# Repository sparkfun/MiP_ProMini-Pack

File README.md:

SparkFun MiP ProMini-Pack
===========================

[*SparkFun MiP ProMini-Pack (DEV-13058)*](https://www.sparkfun.com/products/13058)

The MiP Robotic Platform is the first self-balancing robot that you can drive, dance, plays games, battle with other MiPs, and that you can control via a compatible iOS or Android device. 
With the SparkFun ProMini-Pack you can access the robot’s built-in hacking port to add increased functionality and a miniature Arduino to your MiP. 

Repository Contents
-------------------

* **/Hardware** - Eagle design files (.brd, .sch)
* **/Libraries** - Libraries for use with the <PRODUCT NAME>
* **/Production** - Production panel files (.brd)

Documentation
--------------
* **[Library](https://github.com/sparkfun/SparkFun_MiP_Arduino_Library)** - Arduino library for the MiP ProMini-Pack.
* **[Hookup Guide](https://learn.sparkfun.com/tutorials/hacking-the-mip---promini-pack)** - Basic hookup guide for the MiP ProMini-Pack.
* **[SparkFun Fritzing repo](https://github.com/sparkfun/Fritzing_Parts)** - Fritzing diagrams for SparkFun products.
* **[SparkFun 3D Model repo](https://github.com/sparkfun/3D_Models)** - 3D models of SparkFun products. 
* **[SparkFun Graphical Datasheets](https://github.com/sparkfun/Graphical_Datasheets)** -Graphical Datasheets for various SparkFun products.

License Information
-------------------

This product is _**open source**_! 

Please review the LICENSE.md file for license information. 

If you have any questions or concerns on licensing, please contact techsupport@sparkfun.com.

Distributed as-is; no warranty is given.

- Your friends at SparkFun.

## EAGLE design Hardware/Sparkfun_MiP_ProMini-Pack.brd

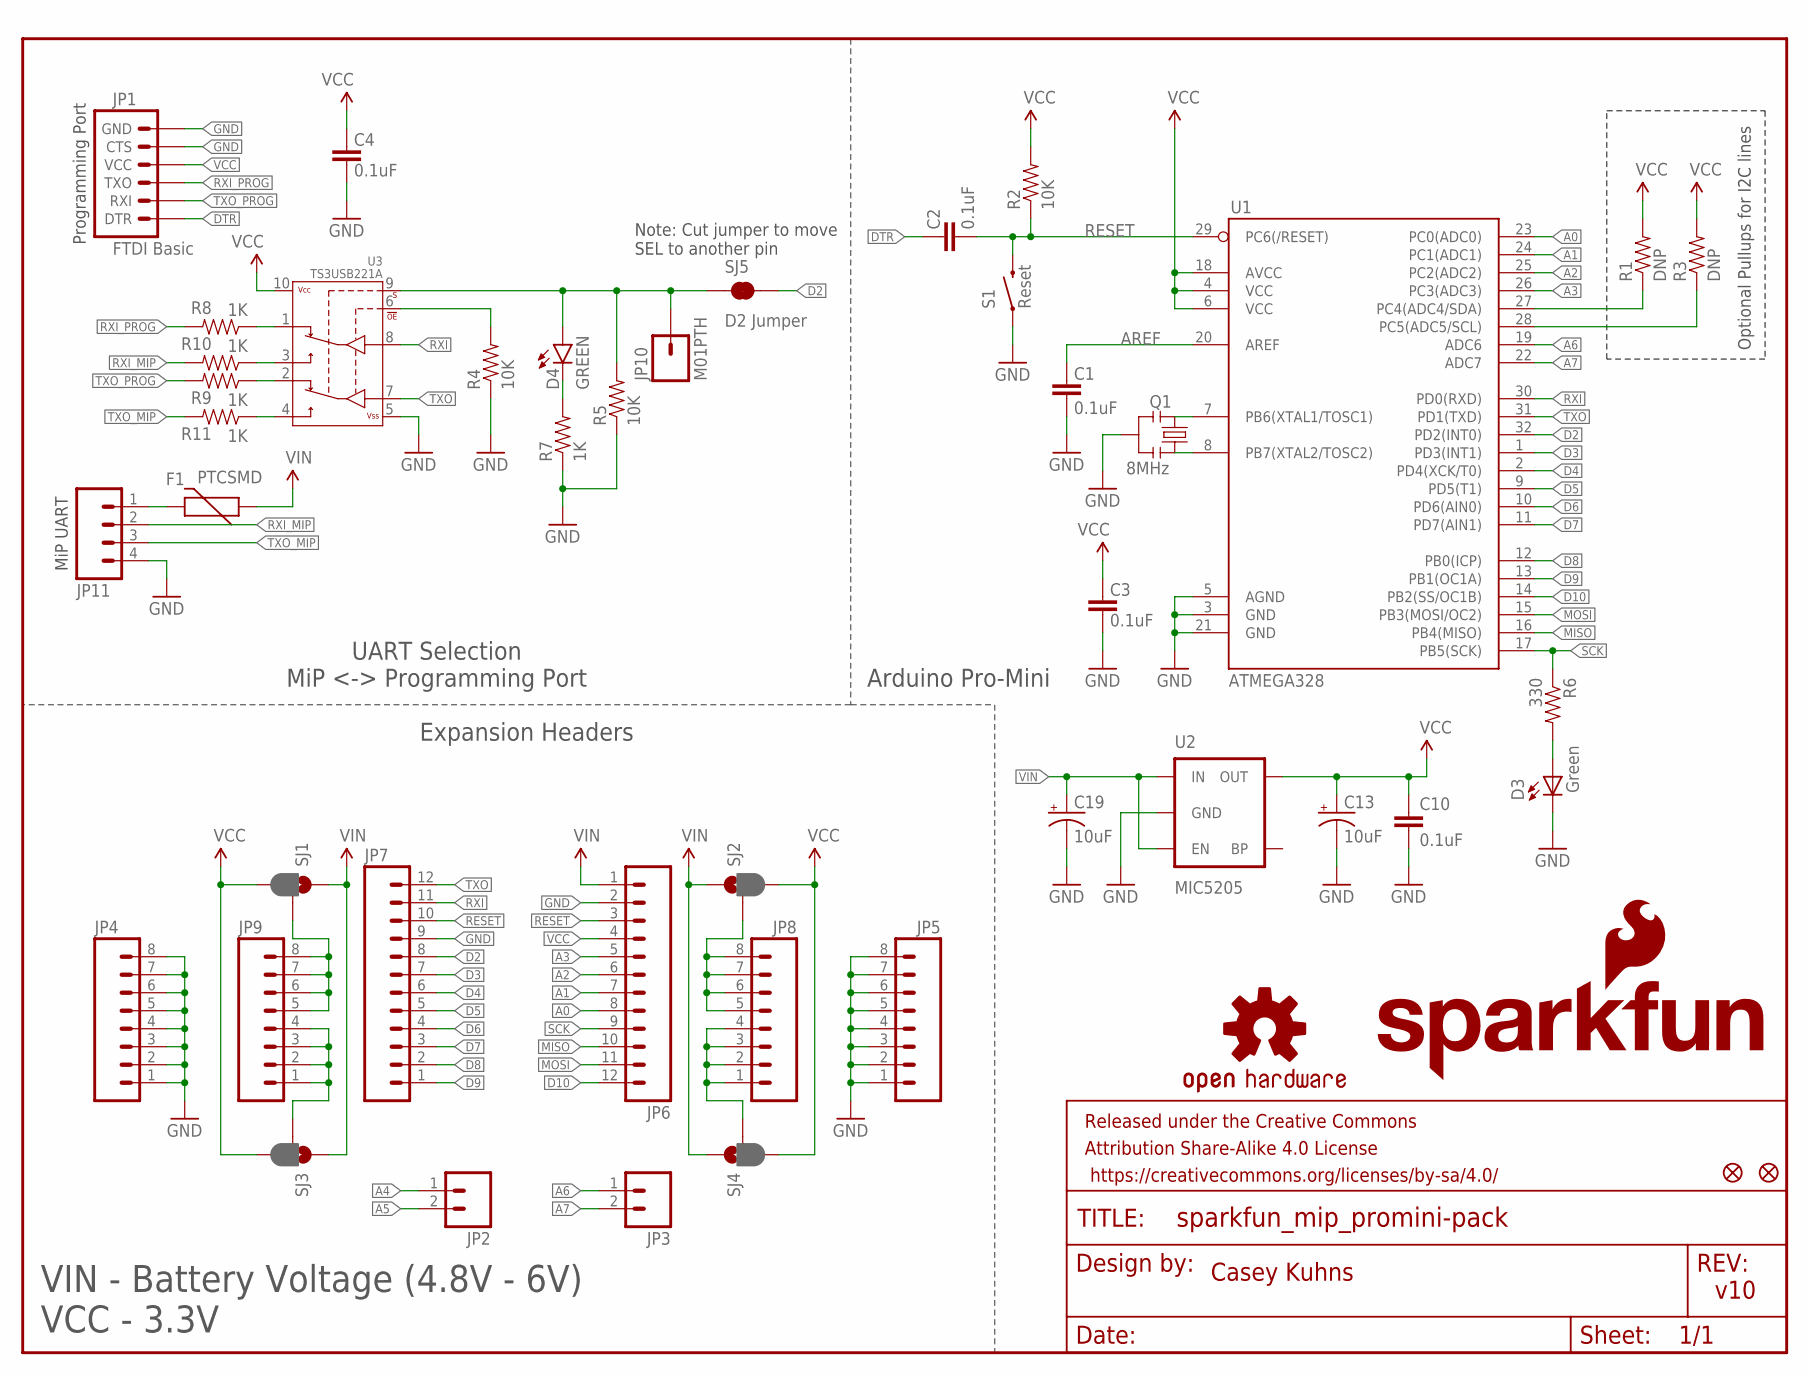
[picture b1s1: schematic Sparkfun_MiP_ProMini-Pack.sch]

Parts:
C1, C2, C3, C4, C10: 0.1uF; 0603-CAP
C13, C19: 10uF; EIA3216
D3: Green; 0603-LED-ALT1
D4: GREEN; LED-0603
F1: PTCSMD; PTC-1206
FID1, FID2: FIDUCIAL1X2; FIDUCIAL-1X2
FRAME1: FRAME-LETTER; CREATIVE_COMMONS
JP1: FTDI Basic; 1X06
JP2, JP3: M02PTH; 1X02
JP4, JP5, JP8, JP9: M081X08; 1X08
JP6, JP7: M12PTH; 1X12
JP10: M01PTH; 1X01
JP11: M04JST; 1X04-1.5MM_JST
LOGO1: SFE_LOGO_NAME_FLAME.1_INCH; SFE_LOGO_NAME_FLAME_.1
LOGO2: OSHW-LOGOS; OSHW-LOGO-S
Q1: 8MHz; RESONATOR-SMD
R1, R3: DNP; 0603-RES
R2, R4, R5: 10K; 0603-RES
R6: 330; 0603-RES
R7, R8, R9, R10, R11: 1K; 0603-RES
S1: Reset; TACTILE-SWITCH-SMD-ALT01
SJ1, SJ2, SJ3, SJ4: JUMPER-PAD-3-2OF3_NC_BY_PASTE; PAD-JUMPER-3-2OF3_NC_BY_PASTE_YES_SILK_FULL_BOX
SJ5: D2 Jumper; PAD-JUMPER-2-NC_BY_TRACE_YES_SILK
U1: ATMEGA328; TQFP32-08
U2: MIC5205; SOT23-5
U3: TS3USB221A; QFN-10-RSE

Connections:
A0: JP6.8, U1.23 (PC0(ADC0))
A1: JP6.7, U1.24 (PC1(ADC1))
A2: JP6.6, U1.25 (PC2(ADC2))
A3: JP6.5, U1.26 (PC3(ADC3))
A4: JP2.1, R1.1, U1.27 (PC4(ADC4/SDA))
A5: JP2.2, R3.1, U1.28 (PC5(ADC5/SCL))
A6: JP3.1, U1.19 (ADC6)
A7: JP3.2, U1.22 (ADC7)
AREF: C1.2, U1.20 (AREF)
D2: JP7.8, SJ5.2, U1.32 (PD2(INT0))
D3: JP7.7, U1.1 (PD3(INT1))
D4: JP7.6, U1.2 (PD4(XCK/T0))
D5: JP7.5, U1.9 (PD5(T1))
D6: JP7.4, U1.10 (PD6(AIN0))
D7: JP7.3, U1.11 (PD7(AIN1))
D8: JP7.2, U1.12 (PB0(ICP))
D9: JP7.1, U1.13 (PB1(OC1A))
D10: JP6.12, U1.14 (PB2(SS/OC1B))
DTR: C2.2, JP1.1 (DTR)
GND: C1.1, C3.1, C4.1, C10.2, C13.C (-), C19.C (-), D3.C, JP1.5 (CTS), JP1.6 (GND), JP4.1, JP4.2, JP4.3, JP4.4, JP4.5, JP4.6, JP4.7, JP4.8, JP5.1, JP5.2, JP5.3, JP5.4, JP5.5, JP5.6, JP5.7, JP5.8, JP6.2, JP7.9, JP11.4, Q1.2, R4.1, R5.1, R7.1, S1.1, U1.3 (GND), U1.5 (AGND), U1.21 (GND), U2.2 (GND), U3.5 (VSS)
MISO: JP6.10, U1.16 (PB4(MISO))
MOSI: JP6.11, U1.15 (PB3(MOSI/OC2))
unnamed: Q1.3, U1.8 (PB7(XTAL2/TOSC2))
unnamed: JP9.5, JP9.6, JP9.7, JP9.8, SJ1.2
unnamed: JP9.1, JP9.2, JP9.3, JP9.4, SJ3.2
unnamed: Q1.1, U1.7 (PB6(XTAL1/TOSC1))
unnamed: JP8.5, JP8.6, JP8.7, JP8.8, SJ2.2
unnamed: JP8.1, JP8.2, JP8.3, JP8.4, SJ4.2
unnamed: D3.A, R6.2
unnamed: D4.C, R7.2
unnamed: R10.1, U3.3 (2D+)
unnamed: R11.1, U3.4 (2D-)
unnamed: R8.1, U3.1 (1D+)
unnamed: R4.2, U3.6 (!OE)
unnamed: R9.1, U3.2 (1D-)
unnamed: F1.2, JP11.1
RESET: C2.1, JP6.3, JP7.10, R2.1, S1.3 (2), U1.29 (PC6(/RESET))
RXI: JP7.11, U1.30 (PD0(RXD)), U3.8 (D+)
RXI_MIP: JP11.2, R10.2
RXI_PROG: JP1.3 (TXO), R8.2
SCK: JP6.9, R6.1, U1.17 (PB5(SCK))
SELECT: D4.A, JP10.1, R5.2, SJ5.1, U3.9 (S)
TXO: JP7.12, U1.31 (PD1(TXD)), U3.7 (D-)
TXO_MIP: JP11.3, R11.2
TXO_PROG: JP1.2 (RXI), R9.2
VCC: C3.2, C4.2, C10.1, C13.A (+), JP1.4 (VCC), JP6.4, R1.2, R2.2, R3.2, SJ1.3, SJ2.3, SJ3.3, SJ4.3, U1.4 (VCC), U1.6 (VCC), U1.18 (AVCC), U2.5 (OUT), U3.10 (VCC)
VIN: C19.A (+), F1.1, JP6.1, SJ1.1, SJ2.1, SJ3.1, SJ4.1, U2.1 (IN), U2.3 (EN)

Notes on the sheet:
Optional Pullups for I2C lines
Casey Kuhns
v10
Note: Cut jumper to move SEL to another pin
MiP UART
Programming Port
UART Selection MiP <-> Programming Port
Expansion Headers
Arduino Pro-Mini
VIN - Battery Voltage (4.8V - 6V) VCC - 3.3V

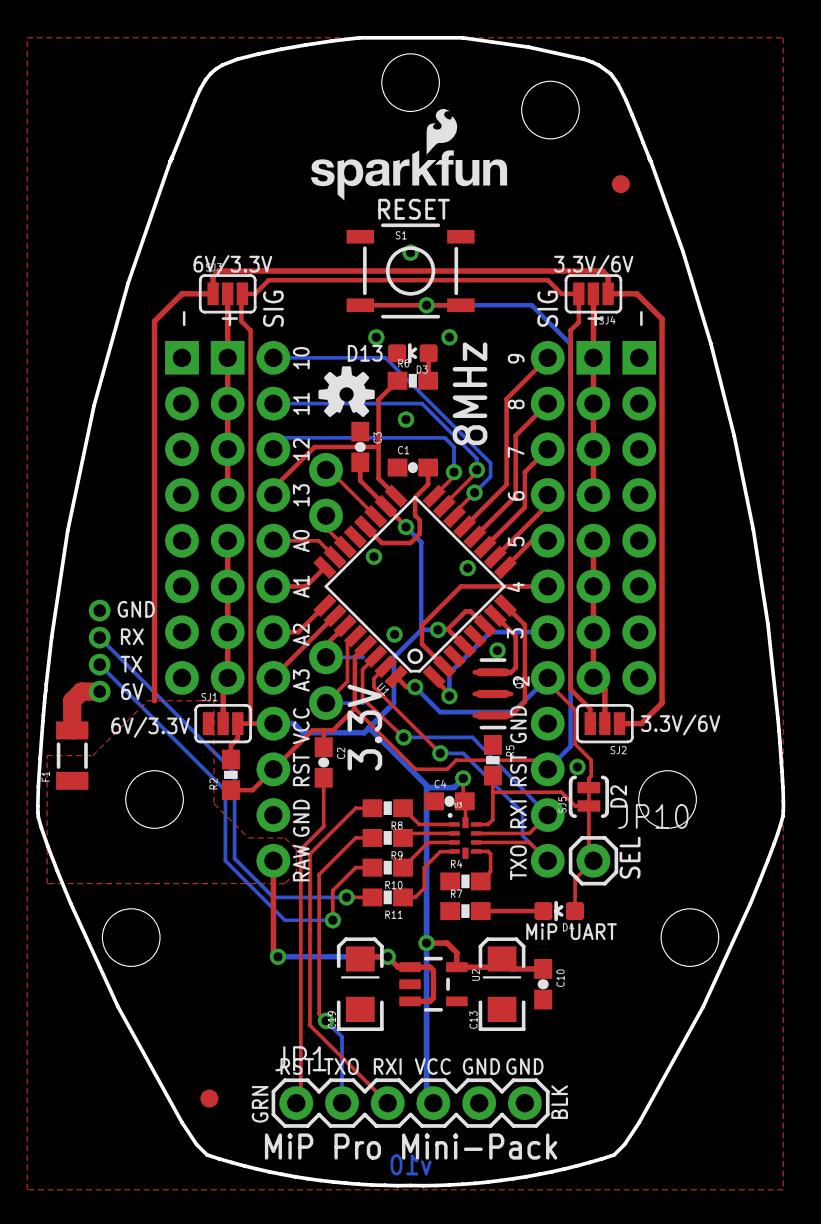
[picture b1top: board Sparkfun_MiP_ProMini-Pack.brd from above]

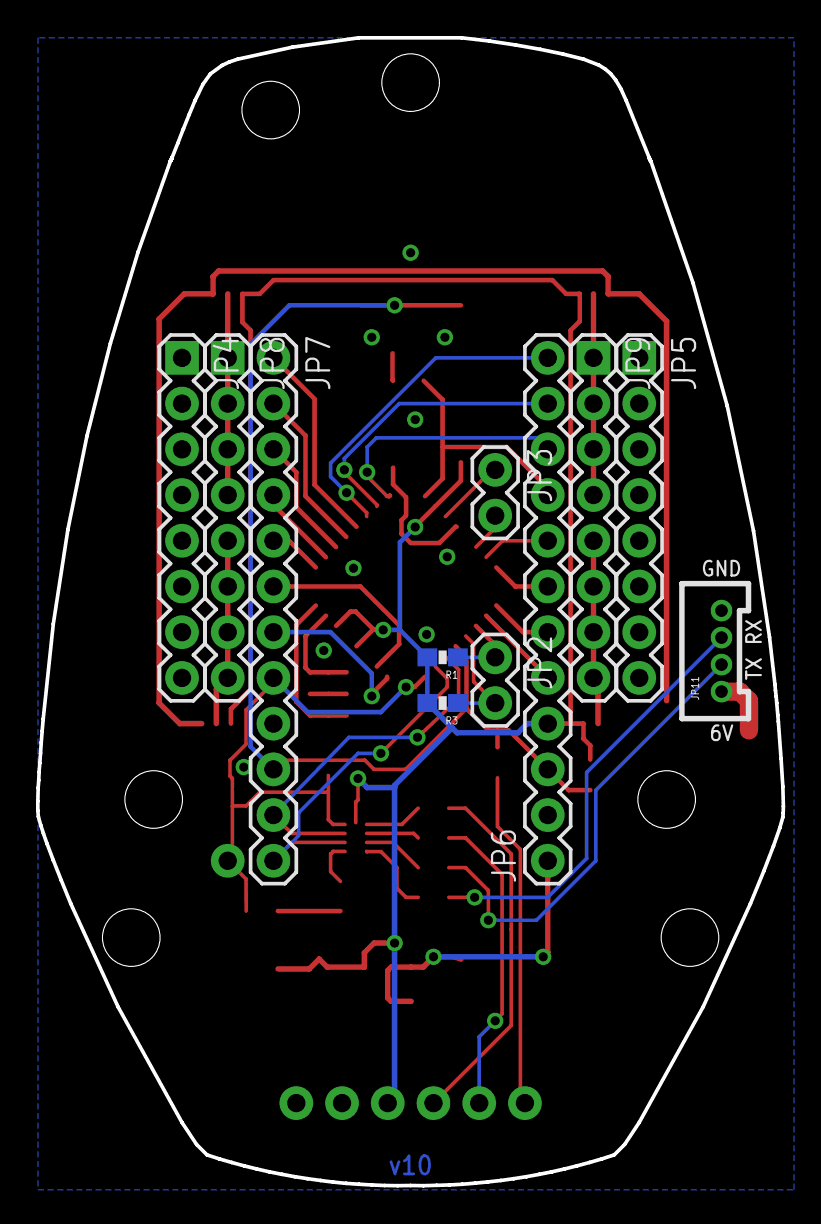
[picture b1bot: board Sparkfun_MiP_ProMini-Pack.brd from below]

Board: 2 copper layers, 41.4 x 63.8 mm, 47 parts (11 on the bottom side), 47 nets.

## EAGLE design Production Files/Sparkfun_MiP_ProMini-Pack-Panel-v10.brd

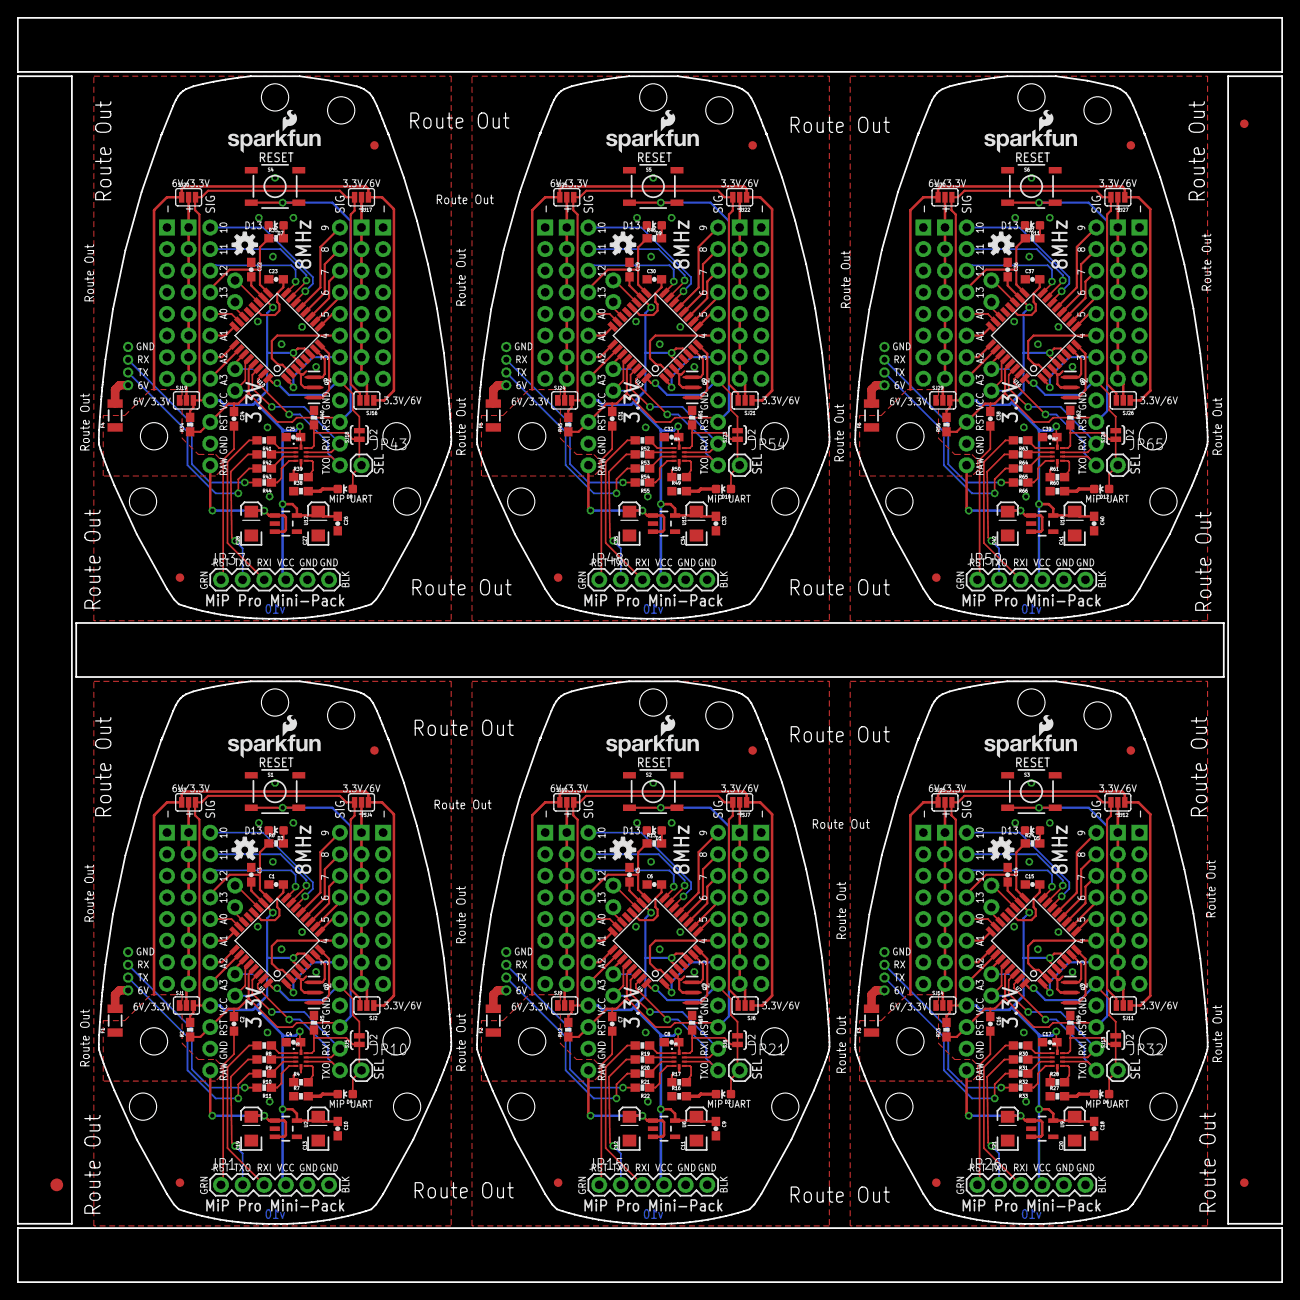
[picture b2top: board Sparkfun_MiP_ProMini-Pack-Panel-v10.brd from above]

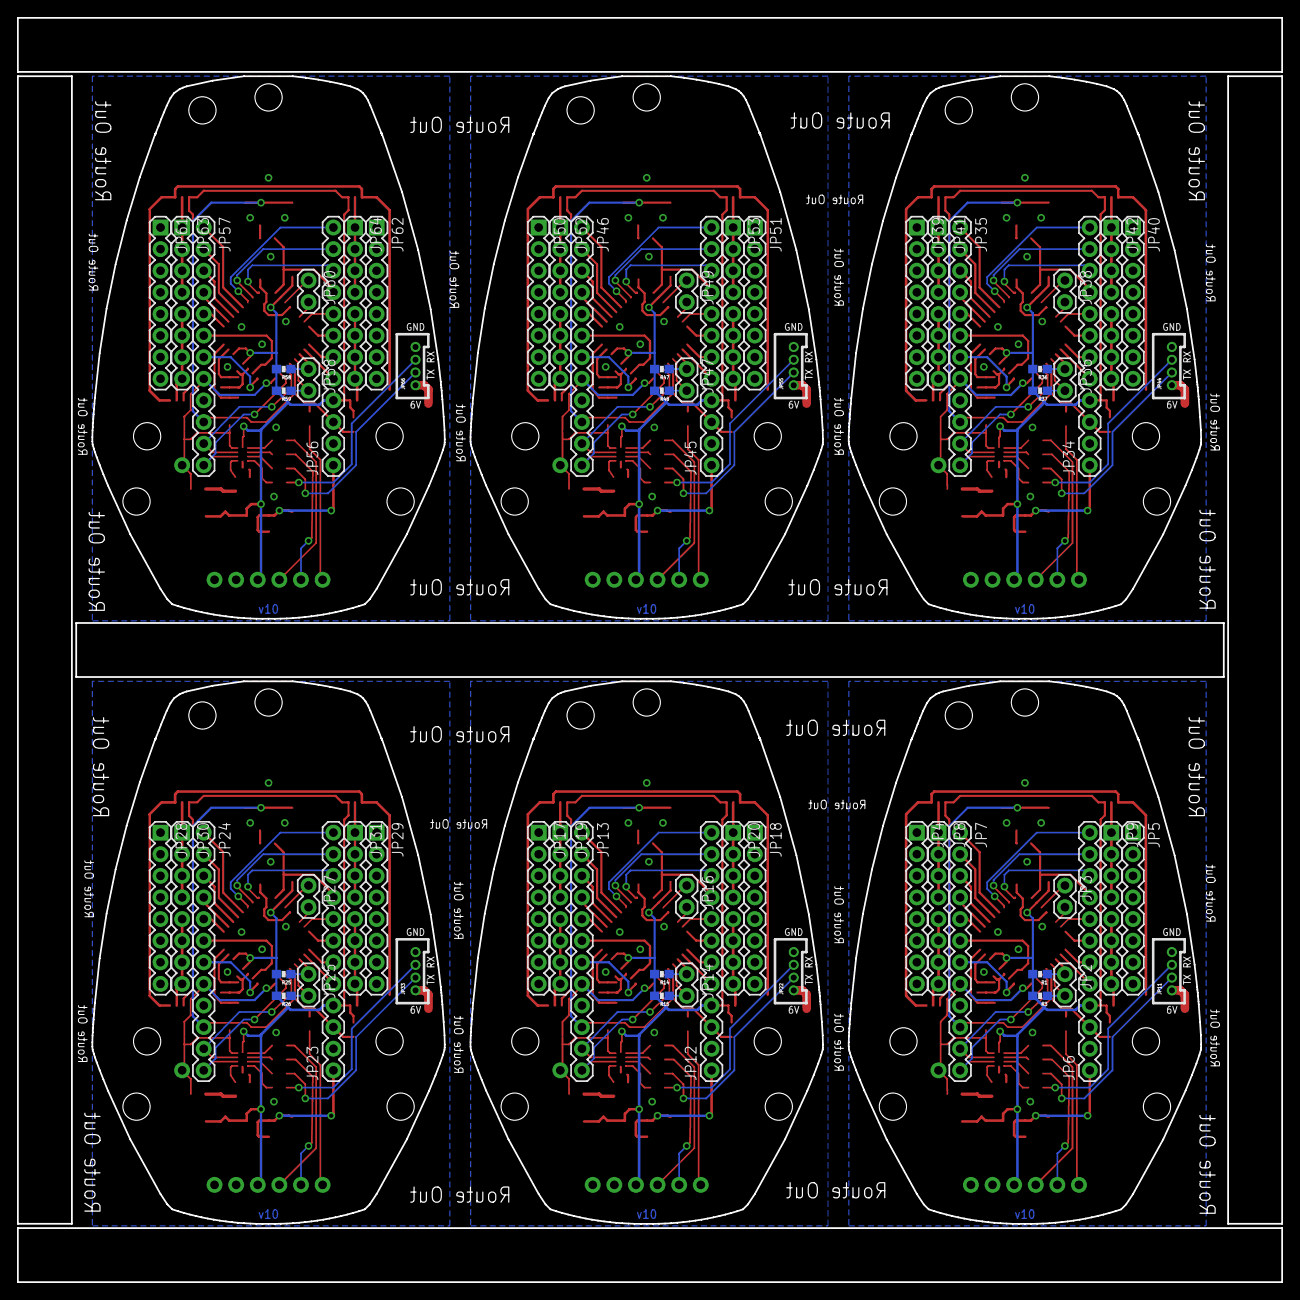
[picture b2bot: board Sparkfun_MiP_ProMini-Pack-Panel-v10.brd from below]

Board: 2 copper layers, 148.6 x 148.6 mm, 279 parts (66 on the bottom side), 282 nets.

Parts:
C1, C2, C3, C4, C5, C6, C7, C8, C9, C10, C14, C15, C16, C17, C18, C22, C23, C24, C25, C26, C29, C30, C31, C32, C33, C36, C37, C38, C39, C40: 0.1uF; 0603-CAP
C11, C12, C13, C19, C20, C21, C27, C28, C34, C35, C41, C42: 10uF; EIA3216
D1, D3, D5, D7, D9, D11: Green; LED-0603
D2, D4, D6, D8, D10, D12: GREEN; LED-0603
E$1: FIDUCIAL-1.5X3
E$4, E$10: FIDUCIAL-1X2
F1, F2, F3, F4, F5, F6: PTCSMD; PTC-1206
FID1, FID2, FID3, FID4, FID5, FID6, FID7, FID8, FID9, FID10, FID11, FID12: FIDUCIAL1X2; FIDUCIAL-1X2
JP1, JP15, JP26, JP37, JP48, JP59: FTDI Basic; 1X06
JP2, JP3, JP14, JP16, JP25, JP27, JP36, JP38, JP47, JP49, JP58, JP60: 1X02
JP4, JP5, JP8, JP9, JP17, JP18, JP19, JP20, JP28, JP29, JP30, JP31, JP39, JP40, JP41, JP42, JP50, JP51, JP52, JP53, JP61, JP62, JP63, JP64: 1X08
JP6, JP7, JP12, JP13, JP23, JP24, JP34, JP35, JP45, JP46, JP56, JP57: 1X12
JP10, JP21, JP32, JP43, JP54, JP65: M01PTH; 1X01
JP11, JP22, JP33, JP44, JP55, JP66: 1X04-1.5MM_JST
LOGO1, LOGO3, LOGO5, LOGO7, LOGO9, LOGO11: SFE_LOGO_NAME_FLAME.1_INCH; SFE_LOGO_NAME_FLAME_.1
LOGO2, LOGO4, LOGO6, LOGO8, LOGO10, LOGO12: OSHW-LOGOS; OSHW-LOGO-S
Q1, Q2, Q3, Q4, Q5, Q6: 8MHz; RESONATOR-SMD
R1, R3, R14, R15, R25, R26, R36, R37, R47, R48, R58, R59: DNP; 0603-RES
R2, R4, R5, R12, R17, R18, R23, R28, R29, R34, R39, R40, R45, R50, R51, R56, R61, R62: 10K; 0603-RES
R6, R13, R24, R35, R46, R57: 330; 0603-RES
R7, R8, R9, R10, R11, R16, R19, R20, R21, R22, R27, R30, R31, R32, R33, R38, R41, R42, R43, R44, R49, R52, R53, R54, R55, R60, R63, R64, R65, R66: 1K; 0603-RES
S1, S2, S3, S4, S5, S6: Reset; TACTILE-SWITCH-SMD
SJ1, SJ2, SJ3, SJ4, SJ6, SJ7, SJ9, SJ10, SJ11, SJ12, SJ14, SJ15, SJ16, SJ17, SJ19, SJ20, SJ21, SJ22, SJ24, SJ25, SJ26, SJ27, SJ29, SJ30: PAD-JUMPER-3-2OF3_NC_BY_PASTE_YES_SILK_FULL_BOX
SJ5, SJ8, SJ13, SJ18, SJ23, SJ28: D2 Jumper; PAD-JUMPER-2-NC_BY_TRACE_YES_SILK
U1, U4, U7, U10, U13, U16: ATMEGA328; TQFP32-08
U2, U6, U9, U12, U15, U18: MIC5205; SOT23-5
U3, U5, U8, U11, U14, U17: TS3USB221A; QFN-10-RSE

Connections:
A0: JP6.8, U1.23
A1: JP6.7, U1.24
A2: JP6.6, U1.25
A3: JP6.5, U1.26
A4: JP2.1, R1.1, U1.27
A5: JP2.2, R3.1, U1.28
A6: JP3.1, U1.19
A7: JP3.2, U1.22
A8: JP14.2, R15.1, U4.28
A9: JP14.1, R14.1, U4.27
A10: JP12.5, U4.26
A11: JP12.6, U4.25
A12: JP12.7, U4.24
A13: JP12.8, U4.23
A14: JP16.1, U4.19
A15: JP16.2, U4.22
A16: JP25.2, R26.1, U7.28
A17: JP25.1, R25.1, U7.27
A18: JP23.5, U7.26
A19: JP23.6, U7.25
A20: JP23.7, U7.24
A21: JP23.8, U7.23
A22: JP27.1, U7.19
A23: JP27.2, U7.22
A24: JP36.2, R37.1, U10.28
A25: JP36.1, R36.1, U10.27
A26: JP34.5, U10.26
A27: JP34.6, U10.25
A28: JP34.7, U10.24
A29: JP34.8, U10.23
A30: JP38.1, U10.19
A31: JP38.2, U10.22
A32: JP47.2, R48.1, U13.28
A33: JP47.1, R47.1, U13.27
A34: JP45.5, U13.26
A35: JP45.6, U13.25
A36: JP45.7, U13.24
A37: JP45.8, U13.23
A38: JP49.1, U13.19
A39: JP49.2, U13.22
A40: JP58.2, R59.1, U16.28
A41: JP58.1, R58.1, U16.27
A42: JP56.5, U16.26
A43: JP56.6, U16.25
A44: JP56.7, U16.24
A45: JP56.8, U16.23
A46: JP60.1, U16.19
A47: JP60.2, U16.22
AREF: C1.2, U1.20
AREF1: C6.2, U4.20
AREF2: C15.2, U7.20
AREF3: C23.2, U10.20
AREF4: C30.2, U13.20
AREF5: C37.2, U16.20
D1: JP13.1, U4.13
D2: JP7.8, SJ5.2, U1.32
D3: JP7.7, U1.1
D4: JP7.6, U1.2
D5: JP7.5, U1.9
D6: JP7.4, U1.10
D7: JP7.3, U1.11
D8: JP7.2, U1.12
D9: JP7.1, U1.13
D10: JP6.12, U1.14
D11: JP13.2, U4.12
D12: JP13.8, SJ8.2, U4.32
D13: JP13.7, U4.1
D14: JP13.6, U4.2
D15: JP13.5, U4.9
D16: JP13.4, U4.10
D17: JP13.3, U4.11
D18: JP12.12, U4.14
D19: JP24.1, U7.13
D20: JP24.2, U7.12
D21: JP24.8, SJ13.2, U7.32
D22: JP24.7, U7.1
D23: JP24.6, U7.2
D24: JP24.5, U7.9
D25: JP24.4, U7.10
D26: JP24.3, U7.11
D27: JP23.12, U7.14
D28: JP35.1, U10.13
D29: JP35.2, U10.12
D30: JP35.8, SJ18.2, U10.32
D31: JP35.7, U10.1
D32: JP35.6, U10.2
D33: JP35.5, U10.9
D34: JP35.4, U10.10
D35: JP35.3, U10.11
D36: JP34.12, U10.14
D37: JP46.1, U13.13
D38: JP46.2, U13.12
D39: JP46.8, SJ23.2, U13.32
D40: JP46.7, U13.1
D41: JP46.6, U13.2
D42: JP46.5, U13.9
D43: JP46.4, U13.10
D44: JP46.3, U13.11
D45: JP45.12, U13.14
D46: JP57.1, U16.13
D47: JP57.2, U16.12
D48: JP57.8, SJ28.2, U16.32
D49: JP57.7, U16.1
D50: JP57.6, U16.2
D51: JP57.5, U16.9
D52: JP57.4, U16.10
D53: JP57.3, U16.11
D54: JP56.12, U16.14
DTR: C2.2, JP1.1
DTR1: C7.2, JP15.1
DTR2: C16.2, JP26.1
DTR3: C24.2, JP37.1
DTR4: C31.2, JP48.1
DTR5: C38.2, JP59.1
GND: C1.1, C3.1, C4.1, C10.2, C13.C, C19.C, D3.C, JP1.5, JP1.6, JP4.1, JP4.2, JP4.3, JP4.4, JP4.5, JP4.6, JP4.7, JP4.8, JP5.1, JP5.2, JP5.3, JP5.4, JP5.5, JP5.6, JP5.7, JP5.8, JP6.2, JP7.9, JP11.4, Q1.2, R4.1, R5.1, R7.1, S1.1, U1.3, U1.5, U1.21, U2.2, U3.5
GND1: C5.1, C6.1, C8.1, C9.2, C11.C, C12.C, D1.C, JP12.2, JP13.9, JP15.5, JP15.6, JP17.1, JP17.2, JP17.3, JP17.4, JP17.5, JP17.6, JP17.7, JP17.8, JP18.1, JP18.2, JP18.3, JP18.4, JP18.5, JP18.6, JP18.7, JP18.8, JP22.4, Q2.2, R16.1, R17.1, R18.1, S2.1, U4.3, U4.5, U4.21, U5.5, U6.2
GND2: C14.1, C15.1, C17.1, C18.2, C20.C, C21.C, D5.C, JP23.2, JP24.9, JP26.5, JP26.6, JP28.1, JP28.2, JP28.3, JP28.4, JP28.5, JP28.6, JP28.7, JP28.8, JP29.1, JP29.2, JP29.3, JP29.4, JP29.5, JP29.6, JP29.7, JP29.8, JP33.4, Q3.2, R27.1, R28.1, R29.1, S3.1, U7.3, U7.5, U7.21, U8.5, U9.2
GND3: C22.1, C23.1, C25.1, C26.2, C27.C, C28.C, D7.C, JP34.2, JP35.9, JP37.5, JP37.6, JP39.1, JP39.2, JP39.3, JP39.4, JP39.5, JP39.6, JP39.7, JP39.8, JP40.1, JP40.2, JP40.3, JP40.4, JP40.5, JP40.6, JP40.7, JP40.8, JP44.4, Q4.2, R38.1, R39.1, R40.1, S4.1, U10.3, U10.5, U10.21, U11.5, U12.2
GND4: C29.1, C30.1, C32.1, C33.2, C34.C, C35.C, D9.C, JP45.2, JP46.9, JP48.5, JP48.6, JP50.1, JP50.2, JP50.3, JP50.4, JP50.5, JP50.6, JP50.7, JP50.8, JP51.1, JP51.2, JP51.3, JP51.4, JP51.5, JP51.6, JP51.7, JP51.8, JP55.4, Q5.2, R49.1, R50.1, R51.1, S5.1, U13.3, U13.5, U13.21, U14.5, U15.2
GND5: C36.1, C37.1, C39.1, C40.2, C41.C, C42.C, D11.C, JP56.2, JP57.9, JP59.5, JP59.6, JP61.1, JP61.2, JP61.3, JP61.4, JP61.5, JP61.6, JP61.7, JP61.8, JP62.1, JP62.2, JP62.3, JP62.4, JP62.5, JP62.6, JP62.7, JP62.8, JP66.4, Q6.2, R60.1, R61.1, R62.1, S6.1, U16.3, U16.5, U16.21, U17.5, U18.2
MISO: JP6.10, U1.16
MISO1: JP12.10, U4.16
MISO2: JP23.10, U7.16
MISO3: JP34.10, U10.16
MISO4: JP45.10, U13.16
MISO5: JP56.10, U16.16
MOSI: JP6.11, U1.15
MOSI1: JP12.11, U4.15
MOSI2: JP23.11, U7.15
MOSI3: JP34.11, U10.15
MOSI4: JP45.11, U13.15
MOSI5: JP56.11, U16.15
unnamed: Q1.3, U1.8
unnamed: JP9.5, JP9.6, JP9.7, JP9.8, SJ1.2
unnamed: JP9.1, JP9.2, JP9.3, JP9.4, SJ3.2
unnamed: Q1.1, U1.7
unnamed: JP8.5, JP8.6, JP8.7, JP8.8, SJ2.2
unnamed: JP8.1, JP8.2, JP8.3, JP8.4, SJ4.2
unnamed: D3.A, R6.2
unnamed: D4.C, R7.2
unnamed: R10.1, U3.3
unnamed: R11.1, U3.4
unnamed: R8.1, U3.1
unnamed: R4.2, U3.6
unnamed: R9.1, U3.2
unnamed: D1.A, R13.2
unnamed: Q2.3, U4.8
unnamed: F1.2, JP11.1
unnamed: Q2.1, U4.7
unnamed: JP19.5, JP19.6, JP19.7, JP19.8, SJ6.2
unnamed: JP20.5, JP20.6, JP20.7, JP20.8, SJ9.2
unnamed: JP20.1, JP20.2, JP20.3, JP20.4, SJ10.2
unnamed: JP19.1, JP19.2, JP19.3, JP19.4, SJ7.2
unnamed: D2.C, R16.2
unnamed: R17.2, U5.6
unnamed: R19.1, U5.1
unnamed: R20.1, U5.2
unnamed: R21.1, U5.3
unnamed: R22.1, U5.4
unnamed: F2.2, JP22.1
unnamed: D5.A, R24.2
unnamed: Q3.3, U7.8
unnamed: Q3.1, U7.7
unnamed: JP30.5, JP30.6, JP30.7, JP30.8, SJ11.2
unnamed: JP31.5, JP31.6, JP31.7, JP31.8, SJ14.2
unnamed: JP31.1, JP31.2, JP31.3, JP31.4, SJ15.2
unnamed: JP30.1, JP30.2, JP30.3, JP30.4, SJ12.2
unnamed: D6.C, R27.2
unnamed: R28.2, U8.6
unnamed: R30.1, U8.1
unnamed: R31.1, U8.2
unnamed: R32.1, U8.3
unnamed: R33.1, U8.4
unnamed: F3.2, JP33.1
unnamed: D7.A, R35.2
unnamed: Q4.3, U10.8
unnamed: Q4.1, U10.7
unnamed: JP41.5, JP41.6, JP41.7, JP41.8, SJ16.2
unnamed: JP42.5, JP42.6, JP42.7, JP42.8, SJ19.2
unnamed: JP42.1, JP42.2, JP42.3, JP42.4, SJ20.2
unnamed: JP41.1, JP41.2, JP41.3, JP41.4, SJ17.2
unnamed: D8.C, R38.2
unnamed: R39.2, U11.6
unnamed: R41.1, U11.1
unnamed: R42.1, U11.2
unnamed: R43.1, U11.3
unnamed: R44.1, U11.4
unnamed: F4.2, JP44.1
unnamed: D9.A, R46.2
unnamed: Q5.3, U13.8
unnamed: Q5.1, U13.7
unnamed: JP52.5, JP52.6, JP52.7, JP52.8, SJ21.2
unnamed: JP53.5, JP53.6, JP53.7, JP53.8, SJ24.2
unnamed: JP53.1, JP53.2, JP53.3, JP53.4, SJ25.2
unnamed: JP52.1, JP52.2, JP52.3, JP52.4, SJ22.2
unnamed: D10.C, R49.2
unnamed: R50.2, U14.6
unnamed: R52.1, U14.1
unnamed: R53.1, U14.2
unnamed: R54.1, U14.3
unnamed: R55.1, U14.4
unnamed: F5.2, JP55.1
unnamed: D11.A, R57.2
unnamed: Q6.3, U16.8
unnamed: Q6.1, U16.7
unnamed: JP63.5, JP63.6, JP63.7, JP63.8, SJ26.2
unnamed: JP64.5, JP64.6, JP64.7, JP64.8, SJ29.2
unnamed: JP64.1, JP64.2, JP64.3, JP64.4, SJ30.2
unnamed: JP63.1, JP63.2, JP63.3, JP63.4, SJ27.2
unnamed: D12.C, R60.2
unnamed: R61.2, U17.6
unnamed: R63.1, U17.1
unnamed: R64.1, U17.2
unnamed: R65.1, U17.3
unnamed: R66.1, U17.4
unnamed: F6.2, JP66.1
RESET: C2.1, JP6.3, JP7.10, R2.1, S1.3, U1.29
RESET1: C7.1, JP12.3, JP13.10, R12.1, S2.3, U4.29
RESET2: C16.1, JP23.3, JP24.10, R23.1, S3.3, U7.29
RESET3: C24.1, JP34.3, JP35.10, R34.1, S4.3, U10.29
RESET4: C31.1, JP45.3, JP46.10, R45.1, S5.3, U13.29
RESET5: C38.1, JP56.3, JP57.10, R56.1, S6.3, U16.29
RXI: JP7.11, U1.30, U3.8
RXI1: JP13.11, U4.30, U5.8
RXI2: JP24.11, U7.30, U8.8
RXI3: JP35.11, U10.30, U11.8
RXI4: JP46.11, U13.30, U14.8
RXI5: JP57.11, U16.30, U17.8
RXI_MIP: JP11.2, R10.2
RXI_MIP1: JP22.2, R21.2
RXI_MIP2: JP33.2, R32.2
RXI_MIP3: JP44.2, R43.2
RXI_MIP4: JP55.2, R54.2
RXI_MIP5: JP66.2, R65.2
RXI_PROG: JP1.3, R8.2
RXI_PROG1: JP15.3, R19.2
RXI_PROG2: JP26.3, R30.2
RXI_PROG3: JP37.3, R41.2
RXI_PROG4: JP48.3, R52.2
RXI_PROG5: JP59.3, R63.2
SCK: JP6.9, R6.1, U1.17
SCK1: JP12.9, R13.1, U4.17
SCK2: JP23.9, R24.1, U7.17
SCK3: JP34.9, R35.1, U10.17
SCK4: JP45.9, R46.1, U13.17
SCK5: JP56.9, R57.1, U16.17
SELECT: D4.A, JP10.1, R5.2, SJ5.1, U3.9
SELECT1: D2.A, JP21.1, R18.2, SJ8.1, U5.9
SELECT2: D6.A, JP32.1, R29.2, SJ13.1, U8.9
SELECT3: D8.A, JP43.1, R40.2, SJ18.1, U11.9
SELECT4: D10.A, JP54.1, R51.2, SJ23.1, U14.9
SELECT5: D12.A, JP65.1, R62.2, SJ28.1, U17.9
TXO: JP7.12, U1.31, U3.7
TXO1: JP13.12, U4.31, U5.7
TXO2: JP24.12, U7.31, U8.7
TXO3: JP35.12, U10.31, U11.7
TXO4: JP46.12, U13.31, U14.7
TXO5: JP57.12, U16.31, U17.7
TXO_MIP: JP11.3, R11.2
TXO_MIP1: JP22.3, R22.2
TXO_MIP2: JP33.3, R33.2
TXO_MIP3: JP44.3, R44.2
TXO_MIP4: JP55.3, R55.2
TXO_MIP5: JP66.3, R66.2
TXO_PROG: JP1.2, R9.2
TXO_PROG1: JP15.2, R20.2
TXO_PROG2: JP26.2, R31.2
TXO_PROG3: JP37.2, R42.2
TXO_PROG4: JP48.2, R53.2
TXO_PROG5: JP59.2, R64.2
VCC: C3.2, C4.2, C10.1, C13.A, JP1.4, JP6.4, R1.2, R2.2, R3.2, SJ1.3, SJ2.3, SJ3.3, SJ4.3, U1.4, U1.6, U1.18, U2.5, U3.10
VCC1: C5.2, C8.2, C9.1, C11.A, JP12.4, JP15.4, R12.2, R14.2, R15.2, SJ6.3, SJ7.3, SJ9.3, SJ10.3, U4.4, U4.6, U4.18, U5.10, U6.5
VCC2: C14.2, C17.2, C18.1, C20.A, JP23.4, JP26.4, R23.2, R25.2, R26.2, SJ11.3, SJ12.3, SJ14.3, SJ15.3, U7.4, U7.6, U7.18, U8.10, U9.5
VCC3: C22.2, C25.2, C26.1, C27.A, JP34.4, JP37.4, R34.2, R36.2, R37.2, SJ16.3, SJ17.3, SJ19.3, SJ20.3, U10.4, U10.6, U10.18, U11.10, U12.5
VCC4: C29.2, C32.2, C33.1, C34.A, JP45.4, JP48.4, R45.2, R47.2, R48.2, SJ21.3, SJ22.3, SJ24.3, SJ25.3, U13.4, U13.6, U13.18, U14.10, U15.5
VCC5: C36.2, C39.2, C40.1, C41.A, JP56.4, JP59.4, R56.2, R58.2, R59.2, SJ26.3, SJ27.3, SJ29.3, SJ30.3, U16.4, U16.6, U16.18, U17.10, U18.5
VIN: C19.A, F1.1, JP6.1, SJ1.1, SJ2.1, SJ3.1, SJ4.1, U2.1, U2.3
VIN1: C12.A, F2.1, JP12.1, SJ6.1, SJ7.1, SJ9.1, SJ10.1, U6.1, U6.3
VIN2: C21.A, F3.1, JP23.1, SJ11.1, SJ12.1, SJ14.1, SJ15.1, U9.1, U9.3
VIN3: C28.A, F4.1, JP34.1, SJ16.1, SJ17.1, SJ19.1, SJ20.1, U12.1, U12.3
VIN4: C35.A, F5.1, JP45.1, SJ21.1, SJ22.1, SJ24.1, SJ25.1, U15.1, U15.3
VIN5: C42.A, F6.1, JP56.1, SJ26.1, SJ27.1, SJ29.1, SJ30.1, U18.1, U18.3

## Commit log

2014-08-19 initial commit ready for review
2014-08-19 removed temp files
2014-08-19 corrected labels, ready for review
2014-08-20 made silk changes and renamed board files to match repo name
2014-11-10 moved components near screw holes. Gives more clearance for hardware
2014-11-17 renamed files
2014-11-17 added lables to servo pins to show pin modes
2014-11-18 addressing issues in github
2014-11-18 added ProdID's to parts
2014-12-01 corrected isolate to 12mil made some layout changes to accomidate.
2014-12-04 created panel v10
2016-02-18 Updating directory structure, fixing README, adding license
2016-02-18 Squashed 'Libraries/Arduino/' content from commit 2675813
    git-subtree-dir: Libraries/Arduino
    git-subtree-split: 2675813431cdc92eb685581f2a9a0be69a096b4c

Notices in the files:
parts and their libraries:
SparkFun-Aesthetics: Licensing: Creative Commons ShareAlike 4.0 International - https://creativecommons.org/licenses/by-sa/4.0
SparkFun-Aesthetics: Released under the Creative Commons Attribution Share-Alike 4.0 License
SparkFun-Aesthetics: https://creativecommons.org/licenses/by-sa/4.0
